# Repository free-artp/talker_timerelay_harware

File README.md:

View this project on [CADLAB.io](https://cadlab.io/node/813). 

# talker_timerelay_harware

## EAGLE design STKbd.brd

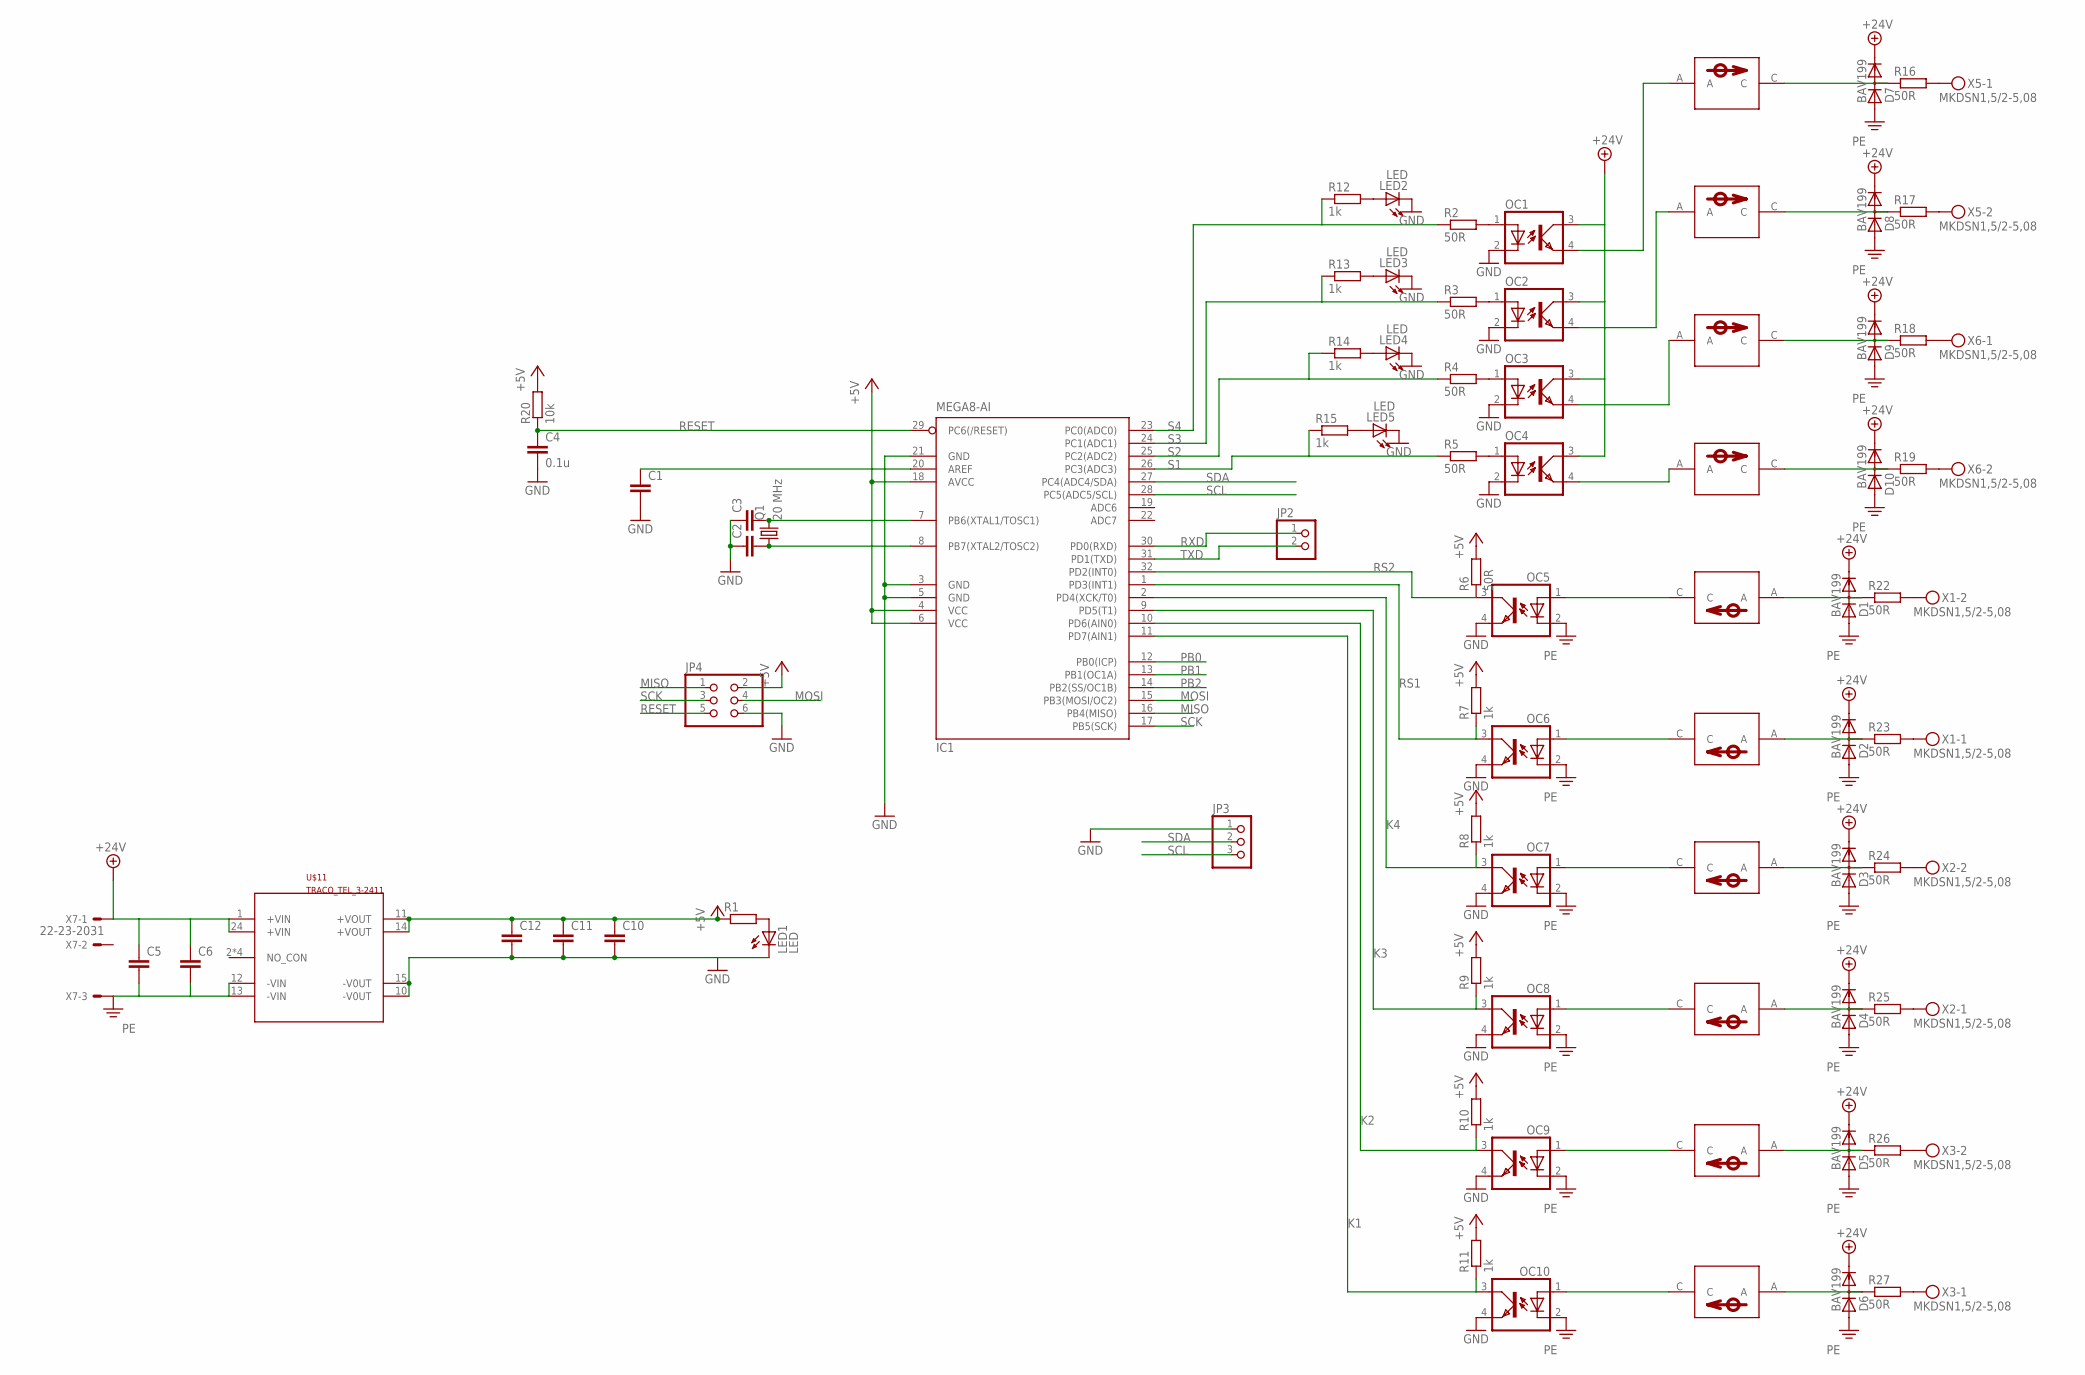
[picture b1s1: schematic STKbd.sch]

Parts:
C1: C-EUC0805K; C0805K
C2, C3, C5, C6, C10, C11, C12: C-EUC0805; C0805
C4: 0.1u; C0805K
D1, D2, D3, D4, D5, D6, D7, D8, D9, D10: BAV199; SOT23
IC1: MEGA8-AI; TQFP32-08
JP2: PINHD-1X2; 1X02
JP3: PINHD-1X3; 1X03
JP4: PINHD-2X3; 2X03
LED1, LED2, LED3, LED4, LED5: LED; LED3MM
OC1, OC2, OC3, OC4, OC5, OC6, OC7, OC8, OC9, OC10: SFH6106REAL; SFH6106
Q1: 20 MHz; SM49
R1: R-EU_R0805; R0805
R2, R3, R4, R5, R6, R16, R17, R18, R19, R22, R23, R24, R25, R26, R27: 50R; R0805
R7, R8, R9, R10, R11, R12, R13, R14, R15: 1k; R0805
R20: 10k; R0805
U$1, U$2, U$3, U$4, U$5, U$6, U$7, U$8, U$9, U$10: NSI45020AT1GSOD-123; SOD123
U$11: TRACO_TEL_3-2411; TEL-3
X1, X2, X3, X5, X6: MKDSN1,5/2-5,08
X7: 22-23-2031

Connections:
+5V: C10.1, C11.1, C12.1, IC1.4 (VCC), IC1.6 (VCC), IC1.18 (AVCC), JP4.2, R1.1, R6.2, R7.2, R8.2, R9.2, R10.2, R11.2, R20.2, U$11.11 (+VOUT), U$11.14 (+VOUT)
+24V: C5.1, C6.1, D1.2 (C), D2.2 (C), D3.2 (C), D4.2 (C), D5.2 (C), D6.2 (C), D7.2 (C), D8.2 (C), D9.2 (C), D10.2 (C), OC1.3 (COL), OC2.3 (COL), OC3.3 (COL), OC4.3 (COL), U$11.1 (+VIN), U$11.24 (+VIN), X7.1
GND: C1.2, C2.1, C3.1, C4.2, C10.2, C11.2, C12.2, IC1.3 (GND), IC1.5 (GND), IC1.21 (GND), JP3.1, JP4.6, LED1.K (C), LED2.K (C), LED3.K (C), LED4.K (C), LED5.K (C), OC1.2 (C), OC2.2 (C), OC3.2 (C), OC4.2 (C), OC5.4 (EMIT), OC6.4 (EMIT), OC7.4 (EMIT), OC8.4 (EMIT), OC9.4 (EMIT), OC10.4 (EMIT), U$11.10 (-V0UT), U$11.15 (-V0UT)
K1: IC1.11 (PD7(AIN1)), OC10.3 (COL), R11.1
K2: IC1.10 (PD6(AIN0)), OC9.3 (COL), R10.1
K3: IC1.9 (PD5(T1)), OC8.3 (COL), R9.1
K4: IC1.2 (PD4(XCK/T0)), OC7.3 (COL), R8.1
MISO: IC1.16 (PB4(MISO)), JP4.1
MOSI: IC1.15 (PB3(MOSI/OC2)), JP4.4
unnamed: OC1.1 (A), R2.2
unnamed: C1.1, IC1.20 (AREF)
unnamed: C3.2, IC1.7 (PB6(XTAL1/TOSC1)), Q1.2
unnamed: C2.2, IC1.8 (PB7(XTAL2/TOSC2)), Q1.1
unnamed: OC2.1 (A), R3.2
unnamed: OC3.1 (A), R4.2
unnamed: OC4.1 (A), R5.2
unnamed: R24.2, X2.2
unnamed: D2.3 (AC), R23.1, U$2.A
unnamed: D7.3 (AC), R16.1, U$7.C
unnamed: D8.3 (AC), R17.1, U$8.C
unnamed: LED2.A, R12.2
unnamed: R16.2, X5.1
unnamed: R17.2, X5.2
unnamed: OC6.1 (A), U$2.C
unnamed: D9.3 (AC), R18.1, U$9.C
unnamed: R18.2, X6.1
unnamed: D10.3 (AC), R19.1, U$10.C
unnamed: R19.2, X6.2
unnamed: LED3.A, R13.2
unnamed: R22.2, X1.2
unnamed: LED4.A, R14.2
unnamed: R26.2, X3.2
unnamed: R23.2, X1.1
unnamed: R25.2, X2.1
unnamed: LED5.A, R15.2
unnamed: OC4.4 (EMIT), U$10.A
unnamed: OC3.4 (EMIT), U$9.A
unnamed: OC2.4 (EMIT), U$8.A
unnamed: OC8.1 (A), U$4.C
unnamed: OC9.1 (A), U$5.C
unnamed: OC10.1 (A), U$6.C
unnamed: OC1.4 (EMIT), U$7.A
unnamed: D3.3 (AC), R24.1, U$3.A
unnamed: D1.3 (AC), R22.1, U$1.A
unnamed: D4.3 (AC), R25.1, U$4.A
unnamed: D5.3 (AC), R26.1, U$5.A
unnamed: D6.3 (AC), R27.1, U$6.A
unnamed: R27.2, X3.1
unnamed: LED1.A, R1.2
unnamed: OC7.1 (A), U$3.C
unnamed: OC5.1 (A), U$1.C
PB0: IC1.12 (PB0(ICP))
PB1: IC1.13 (PB1(OC1A))
PB2: IC1.14 (PB2(SS/OC1B))
PE: C5.2, C6.2, D1.1 (A), D2.1 (A), D3.1 (A), D4.1 (A), D5.1 (A), D6.1 (A), D7.1 (A), D8.1 (A), D9.1 (A), D10.1 (A), OC5.2 (C), OC6.2 (C), OC7.2 (C), OC8.2 (C), OC9.2 (C), OC10.2 (C), U$11.12 (-VIN), U$11.13 (-VIN), X7.3
RESET: C4.1, IC1.29 (PC6(/RESET)), JP4.5, R20.1
RS1: IC1.1 (PD3(INT1)), OC6.3 (COL), R7.1
RS2: IC1.32 (PD2(INT0)), OC5.3 (COL), R6.1
RXD: IC1.30 (PD0(RXD)), JP2.1
S1: IC1.26 (PC3(ADC3)), R5.1, R15.1
S2: IC1.25 (PC2(ADC2)), R4.1, R14.1
S3: IC1.24 (PC1(ADC1)), R3.1, R13.1
S4: IC1.23 (PC0(ADC0)), R2.1, R12.1
SCK: IC1.17 (PB5(SCK)), JP4.3
SCL: IC1.28 (PC5(ADC5/SCL)), JP3.3
SDA: IC1.27 (PC4(ADC4/SDA)), JP3.2
TXD: IC1.31 (PD1(TXD)), JP2.2

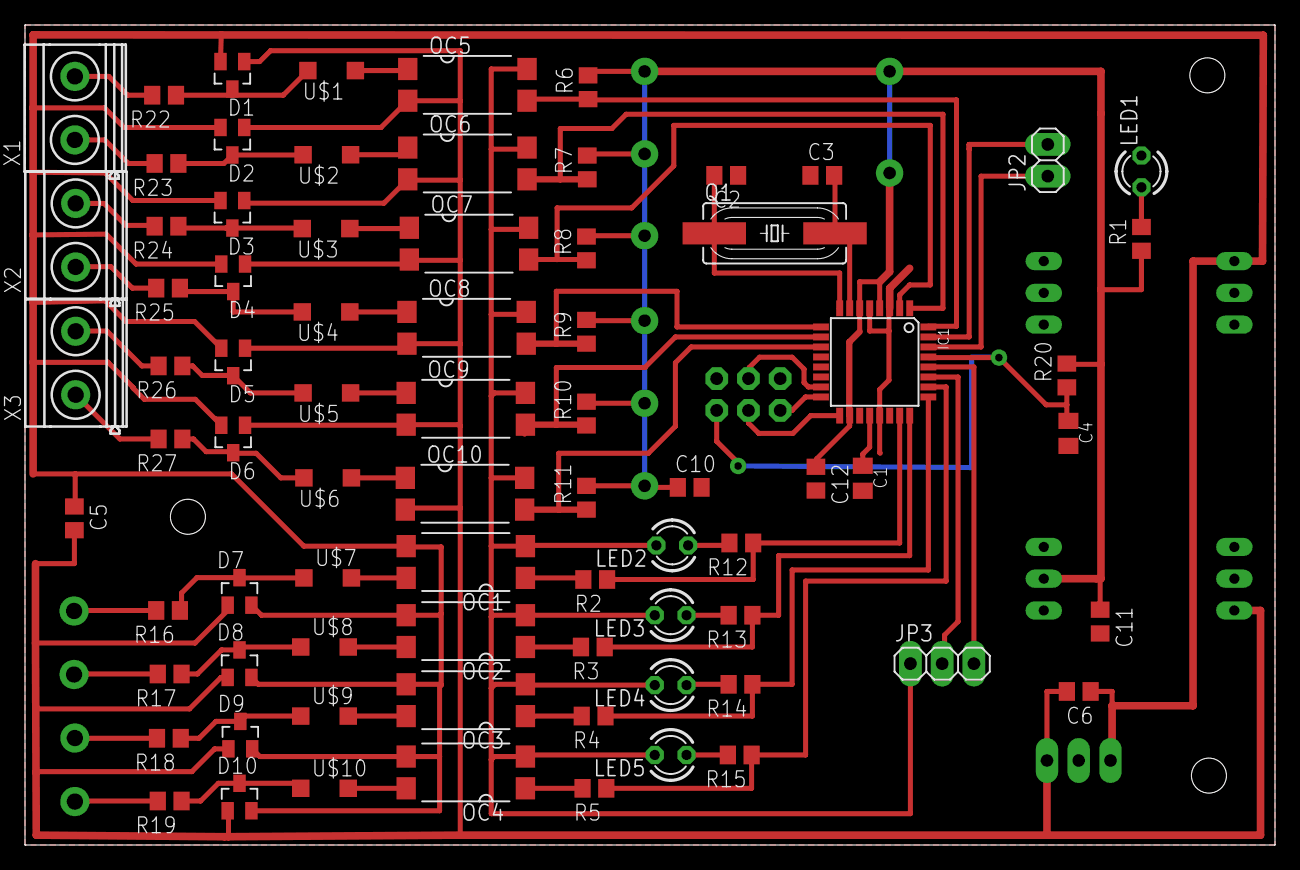
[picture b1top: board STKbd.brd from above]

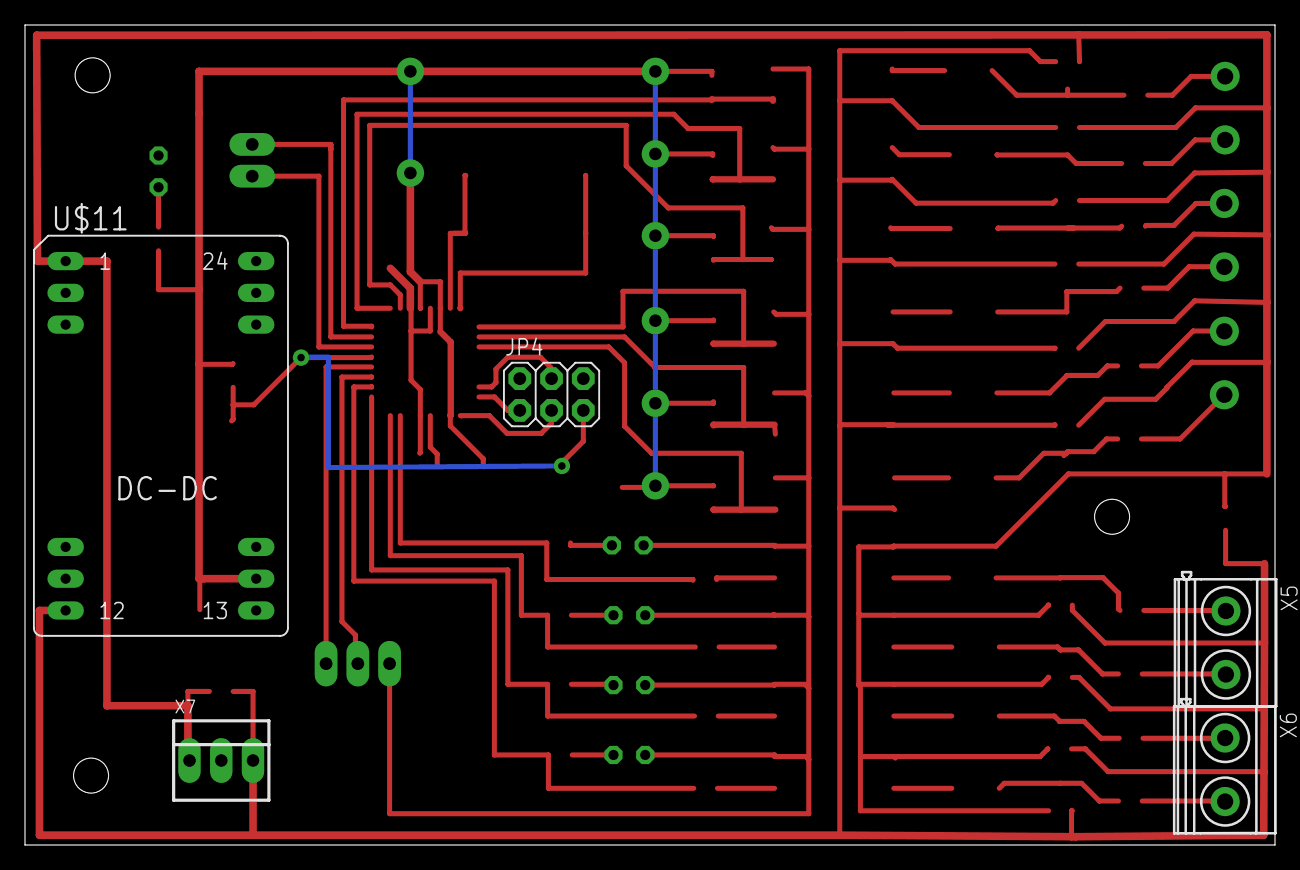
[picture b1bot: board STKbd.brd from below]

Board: 2 copper layers, 100.0 x 65.6 mm, 82 parts (5 on the bottom side), 64 nets.

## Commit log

2017-09-11 Rev 1.0
2017-09-11 rev 1.1 to produce
2017-09-11 rev 1.2 to produce
2017-09-12 rev 1.3 to produce
2018-04-02 Backlink to CADLAB.io has been added.
